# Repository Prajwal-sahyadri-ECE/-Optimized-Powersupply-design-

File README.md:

# Optimized Power Supply & Battery Management System (ICS)

## Overview

This project is an optimized, high-efficiency **Power Management and Multi-Cell Battery Protection System** designed for Industrial Control Systems (ICS) and embedded hardware architectures. The system integrates a **5V Step-Down Switching Regulator**, an **Integrated Li-Ion/LiPo Charger Power Management IC (PMIC)**, and a dedicated **Multi-Cell Battery Monitor & Protection IC** to deliver reliable power regulation, fault protection, and uninterrupted system operation.

---

## Technical Specifications & Architecture

### 1. Buck DC-DC Voltage Regulator (`U1`: LM2596S-5)

* **Function:** High-efficiency step-down DC-DC conversion supplying a stable 5V system rail.
* **Key Components:**
* **Inductor (`L1`):** $33\,\mu\text{H}$ power inductor optimized for switching output ripple filtering.
* **Catch Diode (`D1`):** SS54 Schottky diode for efficient freewheeling action.
* **Capacitors (`C1`, `C2`):** $680\,\mu\text{F}$ input bulk capacitor and $220\,\mu\text{F}$ output smoothing capacitor.

### 2. Power Management & Charger IC (`U2`: IP2326)

* **Function:** Integrated power-path management and lithium battery charging controller.
* **Key Features:**
* **Power Inductor (`L2`):** $2.2\,\mu\text{H}$ low-DCR inductor for high-efficiency charge buck/boost stages.
* **Decoupling/Filter Network:** Output and input ceramic filter capacitors (`C3`, `C5`, `C6` — $10\,\mu\text{F}$ / $22\,\mu\text{F}$).
* **Thermal Monitoring:** External NTC thermistor interface (`TH1` - $100\text{k}\Omega$) for battery over-temperature protection.
* **Status Indication:** Integrated LED indicator (`LED3` / KPT-1608EC) for charging status output.

### 3. Multi-Cell Battery Protection & Monitoring (`U3`: BQ7791500PWR)

* **Function:** Advanced hardware protection for multi-cell Lithium-ion/LiFePO4 battery packs.
* **Key Features:**
* **Cell Balancing & Sensing:** Multi-channel cell tap connections (`VC0`–`VC5`) paired with filter RC networks (`R10`–`R12`, `C10`–`C13`).
* **Charge/Discharge Protection MOSFETs:** Dual high-side/low-side N-channel MOSFET switching control (`Qchg1` & `Qdis1` - IRLR7843TRPBF) driven by high-voltage gate circuitry.
* **Current Sensing:** Low-resistance high-precision current sense resistor (`RCS1` - CRA2512 series) for overcurrent and short-circuit protection.
* **Thermal Sensing:** Onboard NTC thermistor input (`TH3` - $10\text{k}\Omega$) for cell-level temperature monitoring.

### 4. Input/Output Interfaces & Protection

* **Connectors:**
* `J1`: DC Barrel Jack input ($54\text{-}00133$).
* `J2`: Screw terminal output header ($1\times2$).
* `J3`: Multi-pin screw terminal block for battery pack tap/connection interfaces (`B+`, `B-`, `PACK+`, `PACK-`).

* **Overcurrent Protection:** Inline board-level input/output protection fuse (`F1`).
* **Tactile Control Switches:** Push buttons (`S1`, `S2`, `S3`, `S4` - EVP-BB1AAB000) for system control/wake function.
* **Status Indicators:** Diagnostics LEDs (`LED1`, `LED2` - KP-1608SGC) with current-limiting resistors (`R17`, `R22`).

---

## PCB Design & Layout Details

* **Board Type:** 2-Layer High-Density Interconnect PCB.
* **Top Layer:** Signal routing, IC power pads, switching nodes (`LX`, `SW`), and ground copper pouring for optimal thermal dissipation.
* **Bottom Layer:** Solid ground plane return paths and secondary trace routing.
* **Thermal Management:** Exposed thermal ground pads with dense via arrays under `U1`, `U2`, and `U3` to sink heat across layers.
* **High-Current Paths:** Widened power traces for input voltage rails, ground pads, and MOSFET drain/source connections to minimize $I^2R$ conduction losses.

---

```text
├── Hardware/
│   ├── Schematic/
│   │   └── Power Circuit.kicad_sch
│   ├── Layout/
│   │   ├── PCB top layer.png
│   │   ├── PCB bottom layer.png
│   │   └── Power Circuit.kicad_pcb
│   └── Gerber/
│       └── Gerber_Files.zip
├── 3D/
│   └── 3D-view.png
├── LICENSE
└── README.md

```

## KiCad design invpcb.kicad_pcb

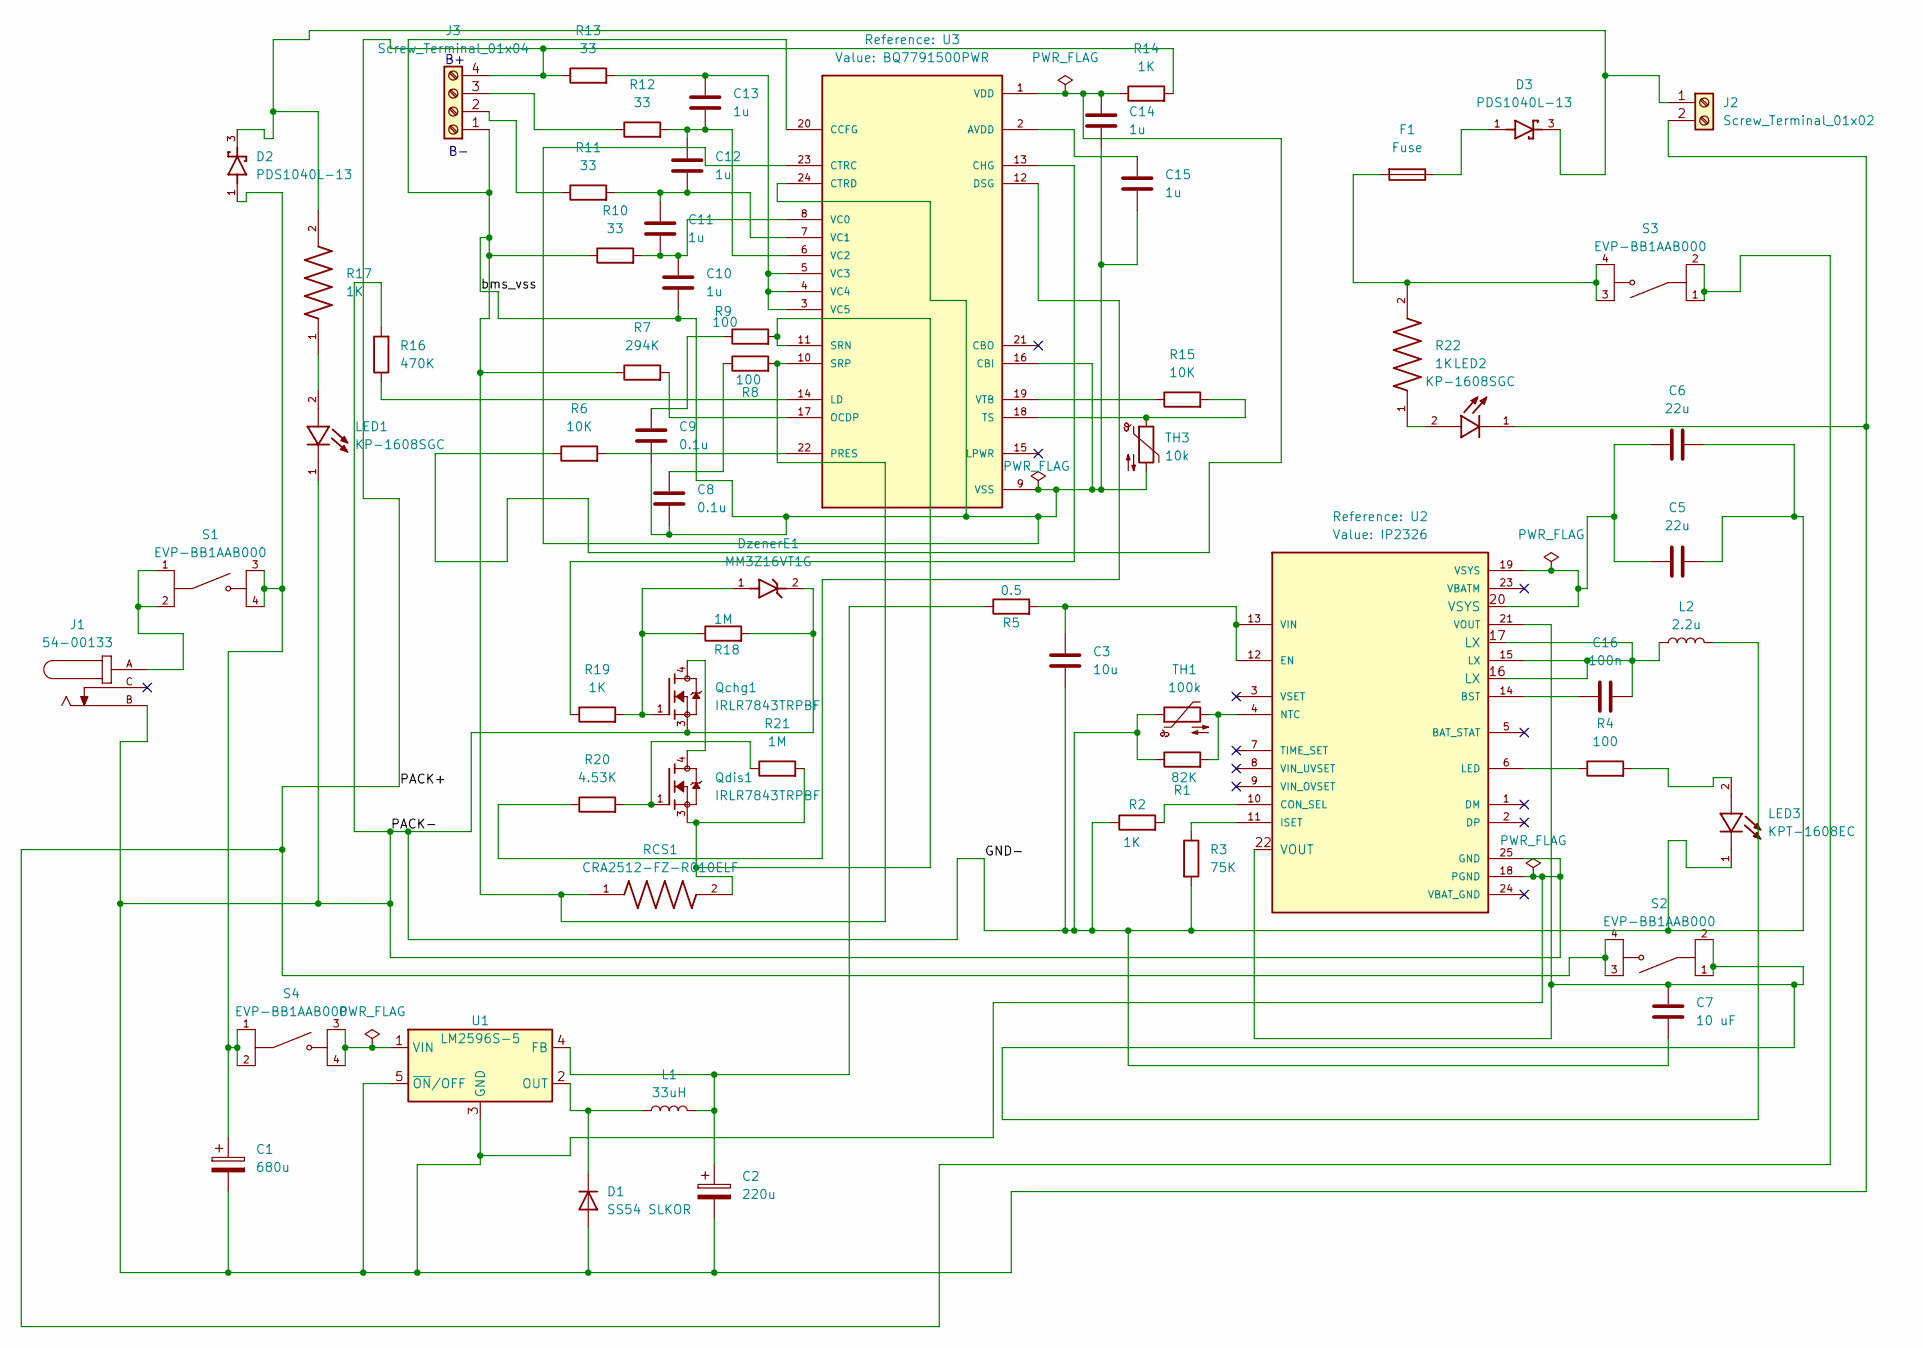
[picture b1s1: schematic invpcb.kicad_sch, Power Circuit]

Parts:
C1: 680u; CHEMI-JA0
C2: 220u; C_Elec_6.3x7.7
C3: 10u; C_1206_3216Metric
C5, C6: 22u; C_0805_2012Metric
C7: 10 uF; C_1206_3216Metric
C8, C9: 0.1u; C_0402_1005Metric
C10, C11, C12, C13, C14, C15: 1u; C_0805_2012Metric
C16: 100n; C_0402_1005Metric
D1: SS54 SLKOR; D_SMA
D2, D3: PDS1040L-13; DIO_PDS1040L-13
DzenerE1: MM3Z16VT1G; D_SOD-323
F1: Fuse; 696101000002
J1: 54-00133; TENSILITY_54-00133
J2: Screw_Terminal_01x02; 2pin terminal TE_282837-2
J3: Screw_Terminal_01x04; TE_282837-4
L1: 33uH; IND_ETQP5M330YFM
L2: 2.2u; IND_SPM6530T-2R2M
LED1, LED2: KP-1608SGC; LED_0402_1005Metric
LED3: KPT-1608EC; LED_0402_1005Metric
Qchg1: IRLR7843TRPBF; TO229P990X239-3_4N
Qdis1: IRLR7843TRPBF; TO229P990X239-3_4N
R1: 82K; R_0402_1005Metric
R2, R14, R17, R19, R22: 1K; R_0603_1608Metric
R3: 75K; R_0402_1005Metric
R4, R8, R9: 100; R_0603_1608Metric
R5: 0.5; RES_RCWE2512R500FKEA
R6, R15: 10K; R_0805_2012Metric
R7: 294K; R_0603_1608Metric
R10, R11, R12, R13: 33; R_1206_3216Metric
R16: 470K; R_0805_2012Metric
R18, R21: 1M; R_1206_3216Metric
R20: 4.53K; R_0201_0603Metric
RCS1: CRA2512-FZ-R010ELF; R_2512_6332Metric
S1, S2, S3, S4: EVP-BB1AAB000; SW_PTS525SM15SMTR2LFS
TH1: 100k; R_0805_2012Metric
TH3: 10k; R_0603_1608Metric
U1: LM2596S-5; TO-263-5_TabPin3
U2: IP2326; ip2326 QFN50P400X400X80-25N
U3: BQ7791500PWR; SOP65P640X120-24N; PARTREV H; DigiKey_Part_Number 296-50995-1-ND

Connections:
/GND-: C1.2, C2.2, C3.2, C5.2, C6.2, C7.2, D1.2 (A), DzenerE1.2, J1.B, J2.2, LED1.1, LED2.1, LED3.1, Qchg1.3, R1.1, R2.1, R3.2, R16.2, R18.2, TH1.1, U1.3 (GND), U1.5 (~ON/OFF), U2.18 (PGND), U2.25 (GND)
/PACK+: J3.4, R13.1, R14.2, S2.3, S2.4, S3.1, S3.2
/bms_vss: C8.2, C9.2, C10.2, C14.2, C15.2, J3.1, R7.1, R8.2, R10.1, RCS1.1, TH3.2, U3.9 (VSS), U3.10 (SRP), U3.16 (CBI), U3.20 (CCFG), U3.23 (CTRC), U3.24 (CTRD)
unnamed: C1.1, D2.1, D2.2, S1.3, S1.4, S4.1, S4.2
unnamed: C7.1, L2.2, S2.1, S2.2, U2.21 (VOUT), U2.22 (VOUT)
unnamed: C8.1, R8.1
unnamed: C9.1, R9.1
unnamed: C16.2, L2.1, U2.15 (LX), U2.16 (LX), U2.17 (LX)
unnamed: D1.1 (K), L1.1, U1.2 (OUT)
unnamed: D3.1, D3.2, F1.1
unnamed: DzenerE1.1, Qchg1.1, R18.1, R19.2
unnamed: F1.2, R22.2, S3.3, S3.4
unnamed: J1.A, S1.1, S1.2
unnamed: D2.3, D3.3, J2.1, R17.2
unnamed: J3.2, R11.1
unnamed: J3.3, R12.1
unnamed: LED1.2, R17.1
unnamed: LED2.2, R22.1
unnamed: LED3.2, R4.2
unnamed: Qchg1.4, Qdis1.4
unnamed: Qdis1.1, R20.2, R21.1
unnamed: C2.1, L1.2, R5.1, U1.4 (FB)
unnamed: S4.3, S4.4, U1.1 (VIN)
unnamed: C16.1, U2.14 (BST)
unnamed: R2.2, U2.10 (CON_SEL)
unnamed: C3.1, R5.2, U2.12 (EN), U2.13 (VIN)
unnamed: R3.1, U2.11 (ISET)
unnamed: R4.1, U2.6 (LED)
unnamed: R1.2, TH1.2, U2.4 (NTC)
unnamed: C15.1, U3.2 (AVDD)
unnamed: R19.1, U3.13 (CHG)
unnamed: R20.1, U3.12 (DSG)
unnamed: R16.1, U3.14 (LD)
unnamed: R7.2, U3.17 (OCDP)
unnamed: R6.2, U3.22 (PRES)
unnamed: Qdis1.3, R9.2, R21.2, RCS1.2, U3.11 (SRN)
unnamed: R15.2, TH3.1, U3.18 (TS)
unnamed: C10.1, C11.2, R10.2, U3.8 (VC0)
unnamed: C11.1, C12.2, R11.2, U3.7 (VC1)
unnamed: C12.1, C13.2, R12.2, U3.6 (VC2)
unnamed: C13.1, R13.2, U3.3 (VC5), U3.4 (VC4), U3.5 (VC3)
unnamed: C14.1, R6.1, R14.1, U3.1 (VDD)
unnamed: R15.1, U3.19 (VTB)
VSYS: C5.1, C6.1, U2.19 (VSYS), U2.20 (VSYS)

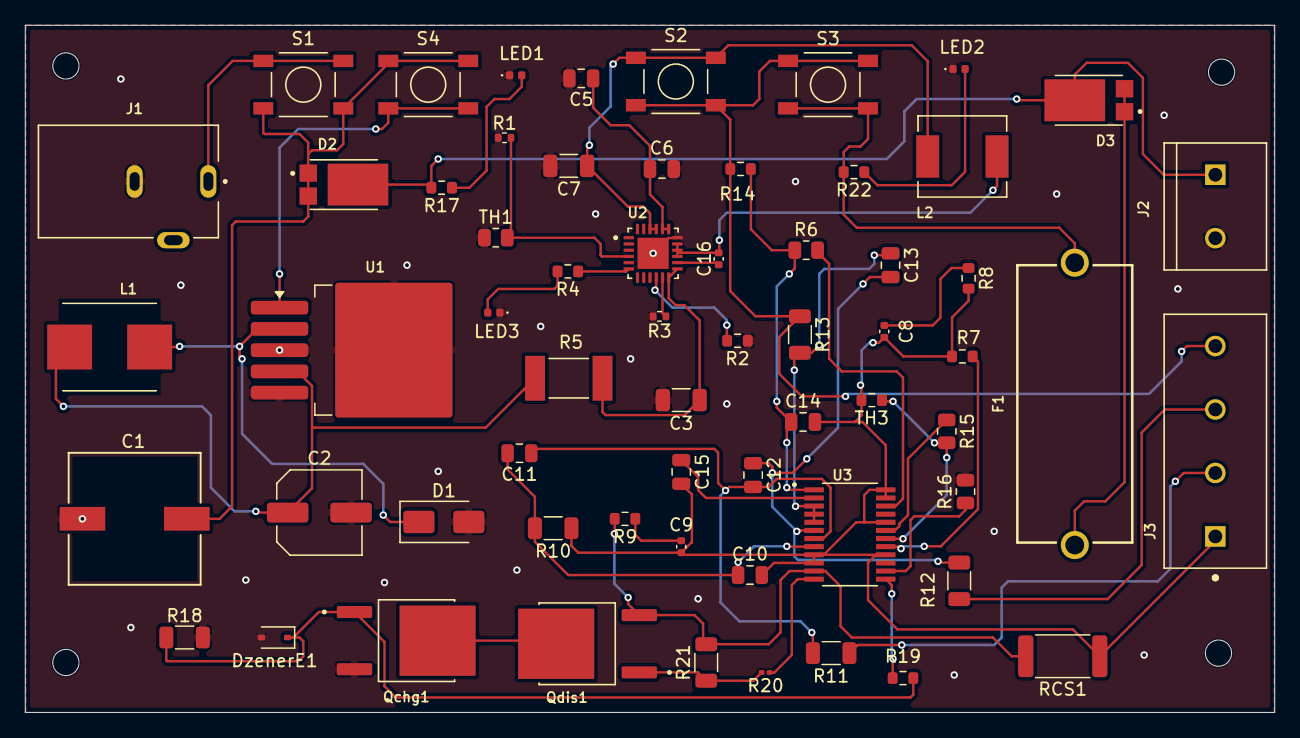
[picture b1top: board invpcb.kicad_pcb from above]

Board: 2 copper layers, 100.0 x 55.0 mm, 62 parts (0 on the bottom side), 44 nets.
